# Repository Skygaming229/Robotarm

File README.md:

# Robotarm
****

Inspiration
- I wanted to create an Robotarm as an Project for my class and will use 5 Servo motors and a STM32 Nucleo64 F446RE Microcontroller and a Joystick

Challenges
- Routing the Jumpercables through the actual arm and making the arm spin and not riping out the cables

Specifications
BOM:

- 5x FS90R 360° Micro Servo - Getriebemotor
- 5x KY-023 - Joystick Modul
- 1x STM32 Nucleo64 F446RE
- 40x Jumpercable male-female
- 40x Jumpercable male-male
- 30x M3x20 Bolt
- 30x M3 Heatset

Others:

- KMK Firmware
- Roboterarm.stl
- Claw from: https://cults3d.com/de/modell-3d/gadget/robot-gripper-9g-micro-servo-for-ar2-or-ar3-robot

Schematic            |  PCB         |   Model
:-------------------------:|:-------------------------:|:------------------------------:
||

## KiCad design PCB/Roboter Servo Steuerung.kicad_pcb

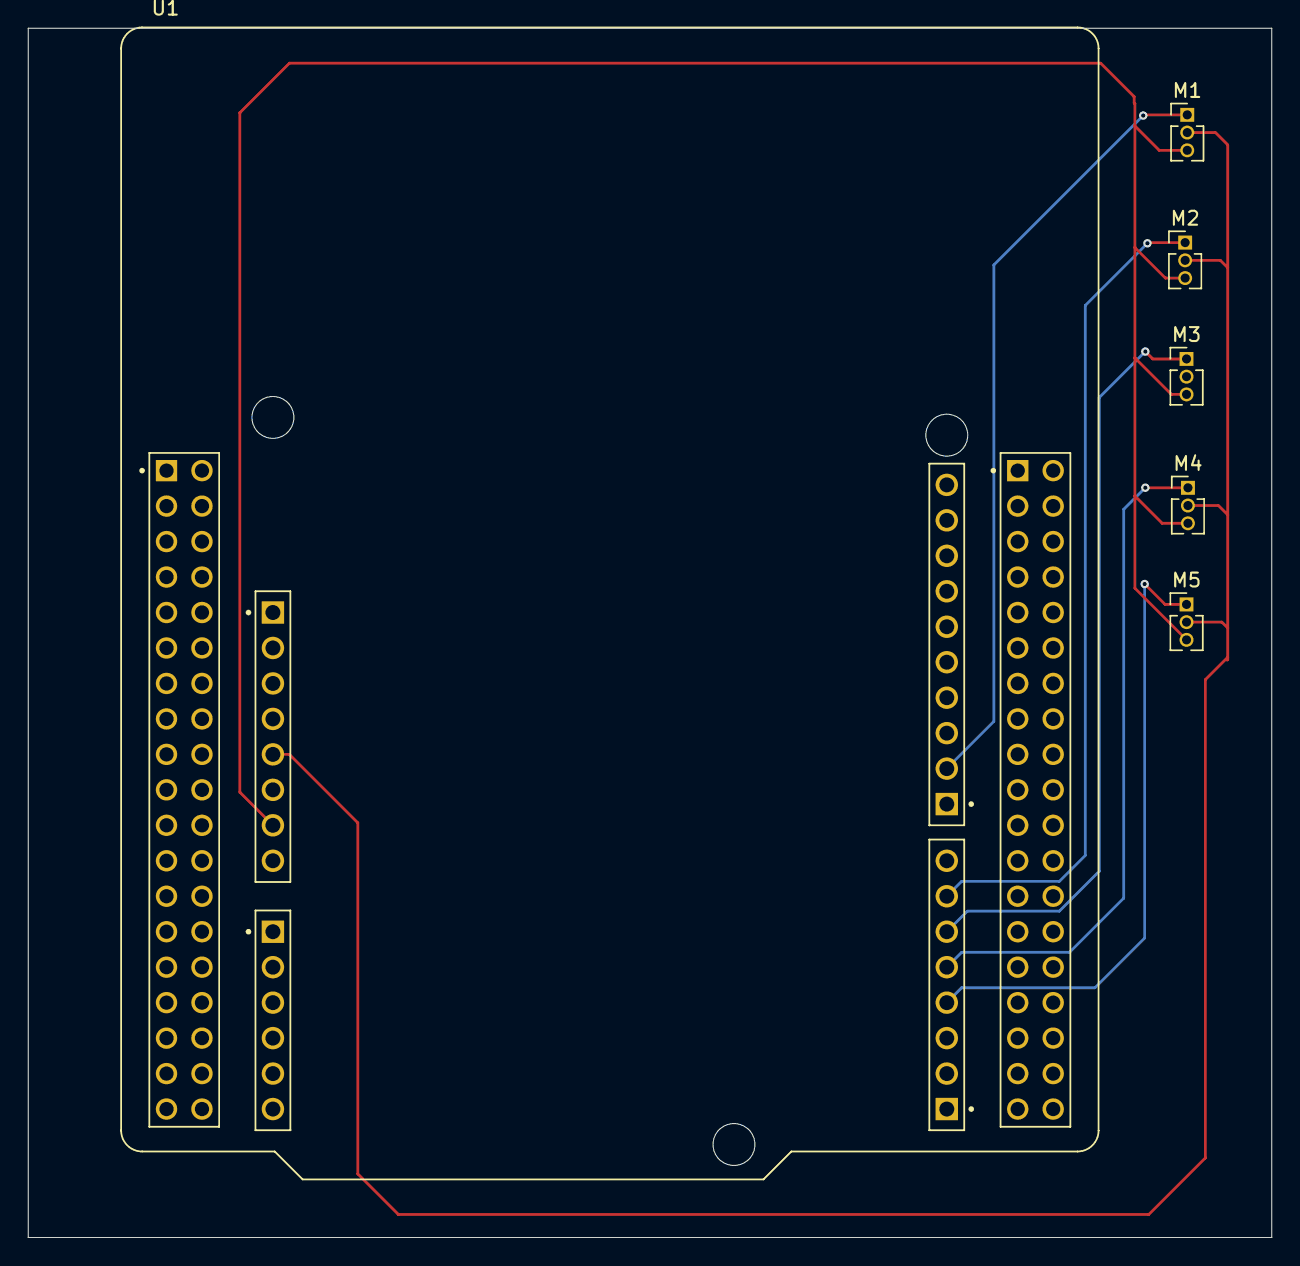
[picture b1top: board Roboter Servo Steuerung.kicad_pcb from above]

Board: 2 copper layers, 89.0 x 86.6 mm, 6 parts (0 on the bottom side), 7 nets.

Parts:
M1, M2, M3, M4, M5: Motor_Servo; PinHeader_1x03_P1.27mm_Vertical
U1: NUCLEO-F446RE; MODULE_NUCLEO-F446RE

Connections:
+5V: M1.2 (+), M2.2 (+), M3.2 (+), M4.2 (+), M5.2 (+), U1.CN6_5 (CN6_+5V)
GND: M1.3 (-), M2.3 (-), M3.3 (-), M4.3 (-), M5.3 (-), U1.CN6_6 (CN6_GND), U1.CN6_7 (CN6_GND)
unnamed: M1.1 (PWM), U1.CN5_2 (D9)
unnamed: M2.1 (PWM), U1.CN9_7 (D6)
unnamed: M3.1 (PWM), U1.CN9_6 (D5)
unnamed: M4.1 (PWM), U1.CN9_5 (D4)
unnamed: M5.1 (PWM), U1.CN9_4 (D3)

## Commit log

2025-12-05 3D Model and PCB
2025-12-05 Fix table formatting and add missing image
2025-12-05 Add claw model reference to README
2025-12-06 KMK erstellen
2025-12-06 Aktualisieren von KMK
2025-12-06 BOM.csv erstellen
2025-12-06 Move project files to organized directories
    Renamed and relocated CAD, PCB, and source files into dedicated folders for better project structure. Added backup and cache files to support KiCad and project management.
